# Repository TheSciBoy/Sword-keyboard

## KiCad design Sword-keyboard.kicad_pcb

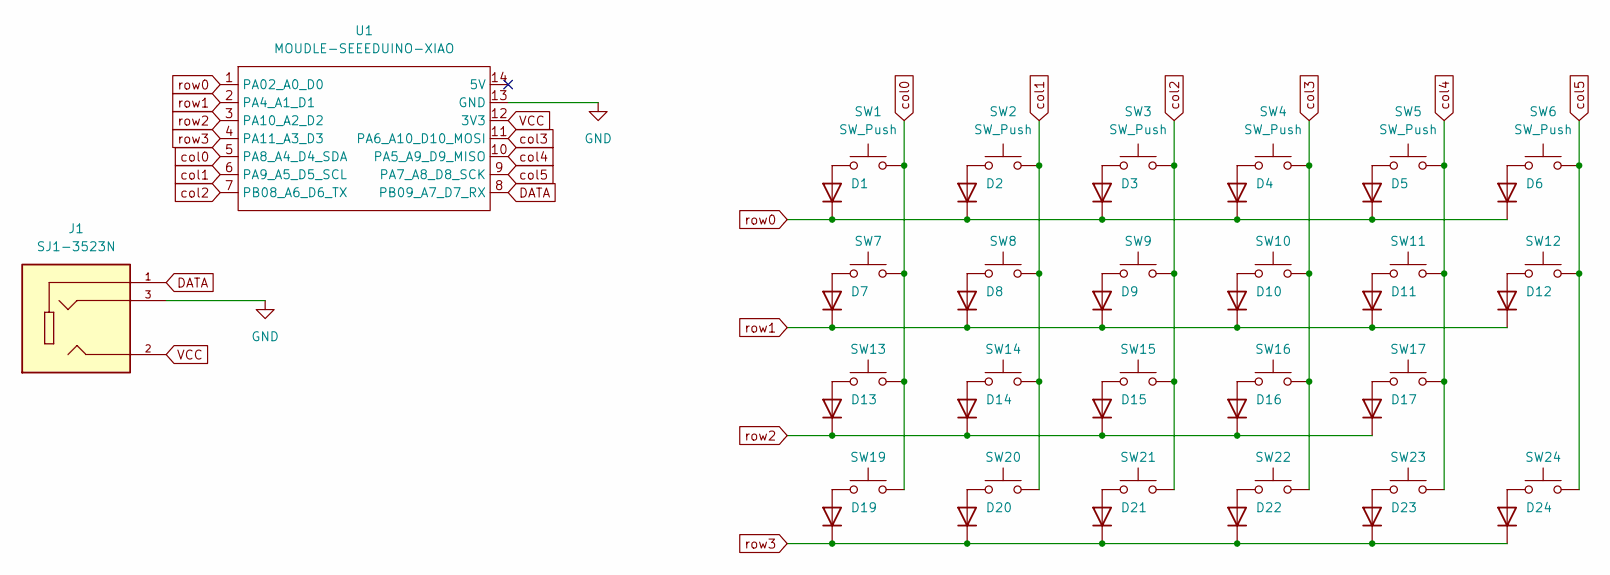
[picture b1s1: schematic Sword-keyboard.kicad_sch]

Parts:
D1, D2, D3, D4, D5, D6, D7, D8, D9, D10, D11, D12, D13, D14, D15, D16, D17, D19, D20, D21, D22, D23, D24: 1N4148; D_DO-35_SOD27_P7.62mm_Horizontal
J1: SJ1-3523N; CUI_SJ1-3523N; PARTREV 1.05
SW1, SW2, SW3, SW4, SW5, SW6, SW7, SW8, SW9, SW10, SW11, SW12, SW13, SW14, SW15, SW16, SW17, SW19, SW20, SW21, SW22, SW23, SW24: SW_Push; SW_MX_reversible
U1: MOUDLE-SEEEDUINO-XIAO; Seeed XIAO RP2040

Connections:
DATA: J1.1, U1.8 (PB09_A7_D7_RX)
GND: J1.3, U1.13 (GND)
unnamed: D1.2 (A), SW1.1
unnamed: D2.2 (A), SW2.1
unnamed: D3.2 (A), SW3.1
unnamed: D4.2 (A), SW4.1
unnamed: D5.2 (A), SW5.1
unnamed: D6.2 (A), SW6.1
unnamed: D7.2 (A), SW7.1
unnamed: D8.2 (A), SW8.1
unnamed: D9.2 (A), SW9.1
unnamed: D10.2 (A), SW10.1
unnamed: D11.2 (A), SW11.1
unnamed: D12.2 (A), SW12.1
unnamed: D13.2 (A), SW13.1
unnamed: D14.2 (A), SW14.1
unnamed: D15.2 (A), SW15.1
unnamed: D16.2 (A), SW16.1
unnamed: D17.2 (A), SW17.1
unnamed: D19.2 (A), SW19.1
unnamed: D20.2 (A), SW20.1
unnamed: D21.2 (A), SW21.1
unnamed: D22.2 (A), SW22.1
unnamed: D23.2 (A), SW23.1
unnamed: D24.2 (A), SW24.1
VCC: J1.2, U1.12 (3V3)
col0: SW1.2, SW7.2, SW13.2, SW19.2, U1.5 (PA8_A4_D4_SDA)
col1: SW2.2, SW8.2, SW14.2, SW20.2, U1.6 (PA9_A5_D5_SCL)
col2: SW3.2, SW9.2, SW15.2, SW21.2, U1.7 (PB08_A6_D6_TX)
col3: SW4.2, SW10.2, SW16.2, SW22.2, U1.11 (PA6_A10_D10_MOSI)
col4: SW5.2, SW11.2, SW17.2, SW23.2, U1.10 (PA5_A9_D9_MISO)
col5: SW6.2, SW12.2, SW24.2, U1.9 (PA7_A8_D8_SCK)
row0: D1.1 (K), D2.1 (K), D3.1 (K), D4.1 (K), D5.1 (K), D6.1 (K), U1.1 (PA02_A0_D0)
row1: D7.1 (K), D8.1 (K), D9.1 (K), D10.1 (K), D11.1 (K), D12.1 (K), U1.2 (PA4_A1_D1)
row2: D13.1 (K), D14.1 (K), D15.1 (K), D16.1 (K), D17.1 (K), U1.3 (PA10_A2_D2)
row3: D19.1 (K), D20.1 (K), D21.1 (K), D22.1 (K), D23.1 (K), D24.1 (K), U1.4 (PA11_A3_D3)

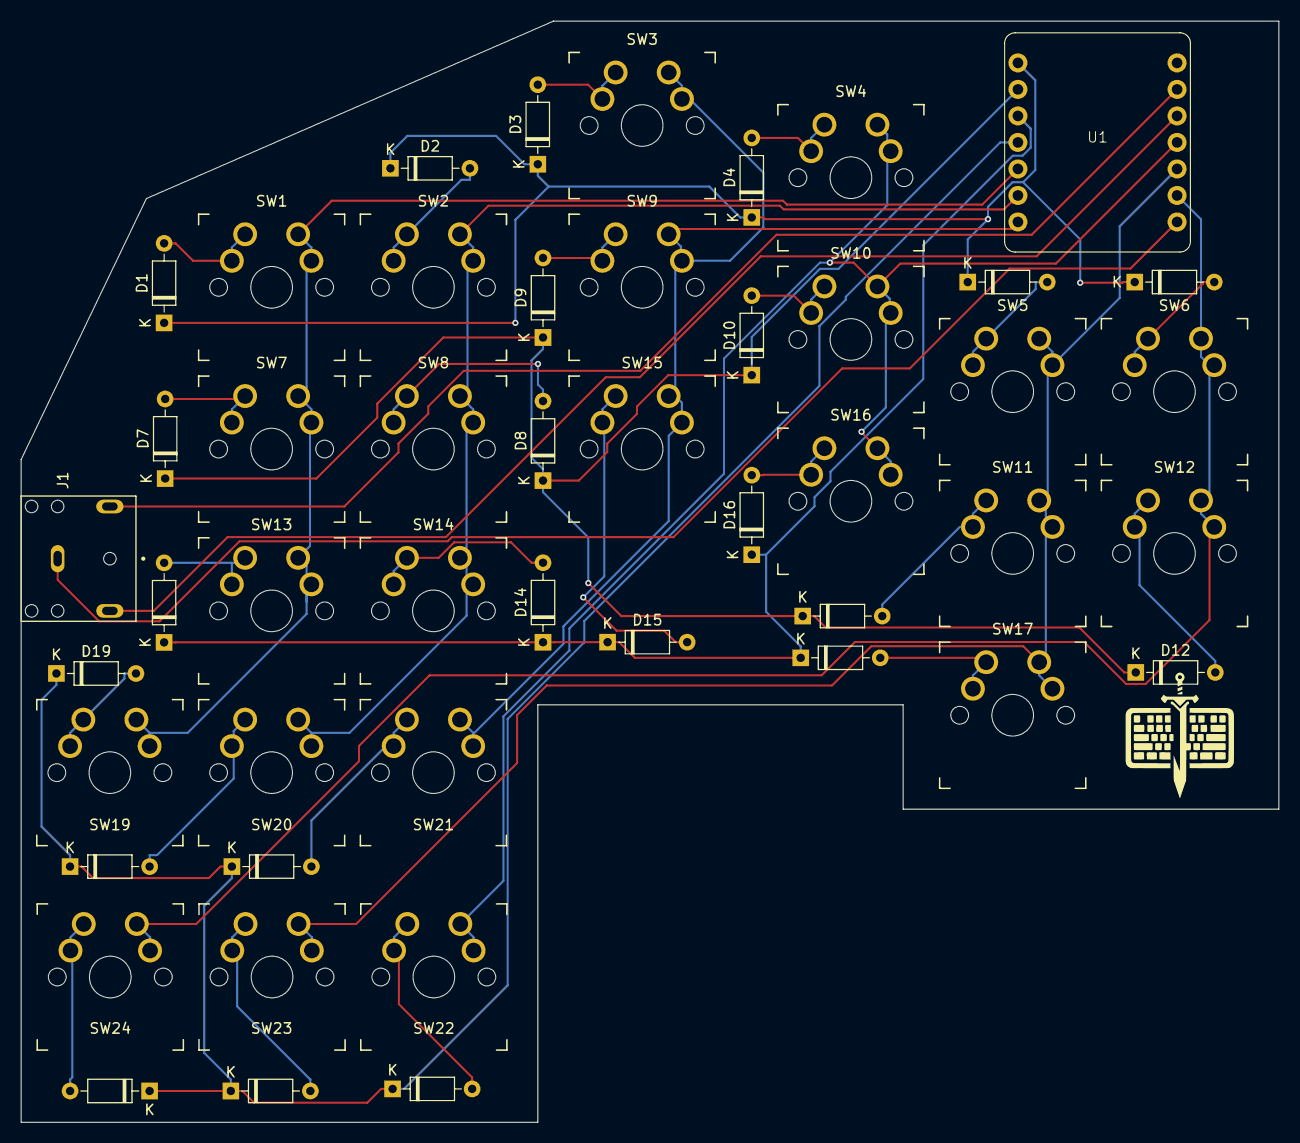
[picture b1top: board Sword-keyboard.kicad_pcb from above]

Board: 2 copper layers, 120.5 x 105.5 mm, 48 parts (0 on the bottom side), 36 nets.

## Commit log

2024-04-28 First iteration
2024-04-28 Exchanged audio jack
2024-04-28 Did an autorouting with freerouting
2024-04-28 Reduced the outline of the board a little.
2024-04-28 New export to freerouter to route
2024-04-28 Routing with 90 degree angles since we have one of those right in the path.
2024-04-28 Routed everything.
2024-04-28 Added silkscreen logo
2024-04-28 Gerber version 1.0
